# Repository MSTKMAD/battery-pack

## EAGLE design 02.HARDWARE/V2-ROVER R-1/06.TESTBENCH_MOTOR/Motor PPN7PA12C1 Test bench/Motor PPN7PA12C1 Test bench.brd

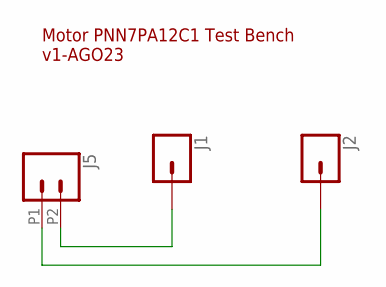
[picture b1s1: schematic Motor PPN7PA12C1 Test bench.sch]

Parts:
J1, J2: CONN_01; 1X01
J5: CONN_022.54MM_SCREWTERM; 1X02_2.54_SCREWTERM

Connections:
unnamed: J2.1, J5.P1 (1)
unnamed: J1.1, J5.P2 (2)

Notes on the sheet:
Motor PNN7PA12C1 Test Bench v1-AGO23

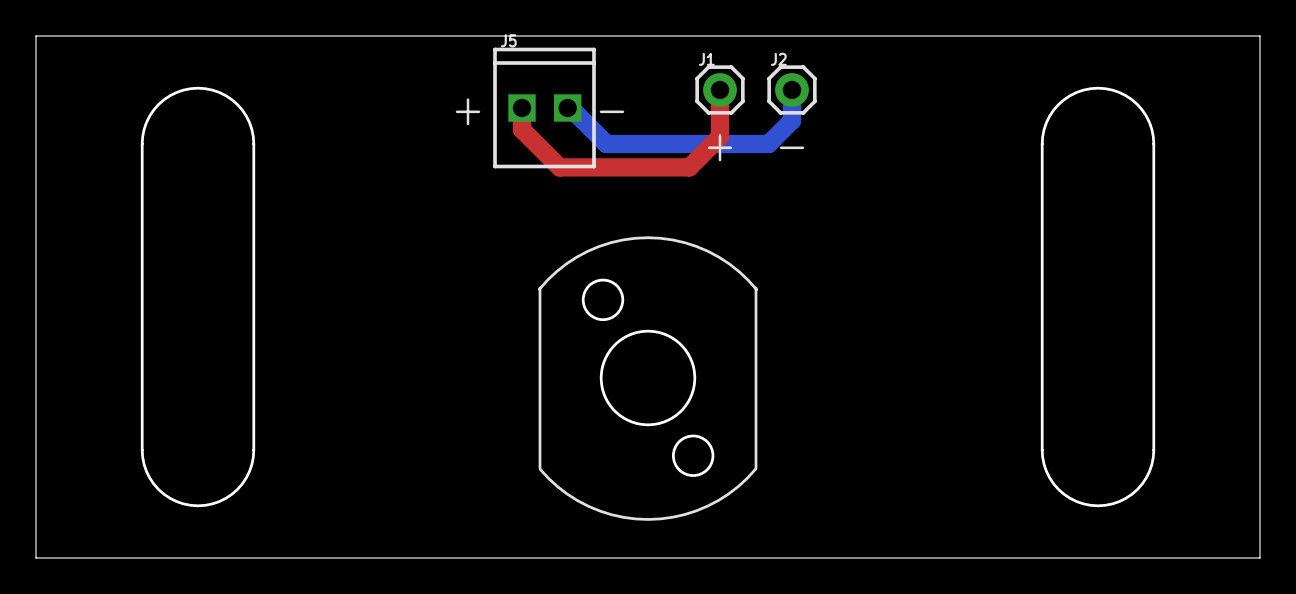
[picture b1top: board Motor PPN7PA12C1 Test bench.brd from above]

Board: 2 copper layers, 68.0 x 29.0 mm, 3 parts (0 on the bottom side), 2 nets.

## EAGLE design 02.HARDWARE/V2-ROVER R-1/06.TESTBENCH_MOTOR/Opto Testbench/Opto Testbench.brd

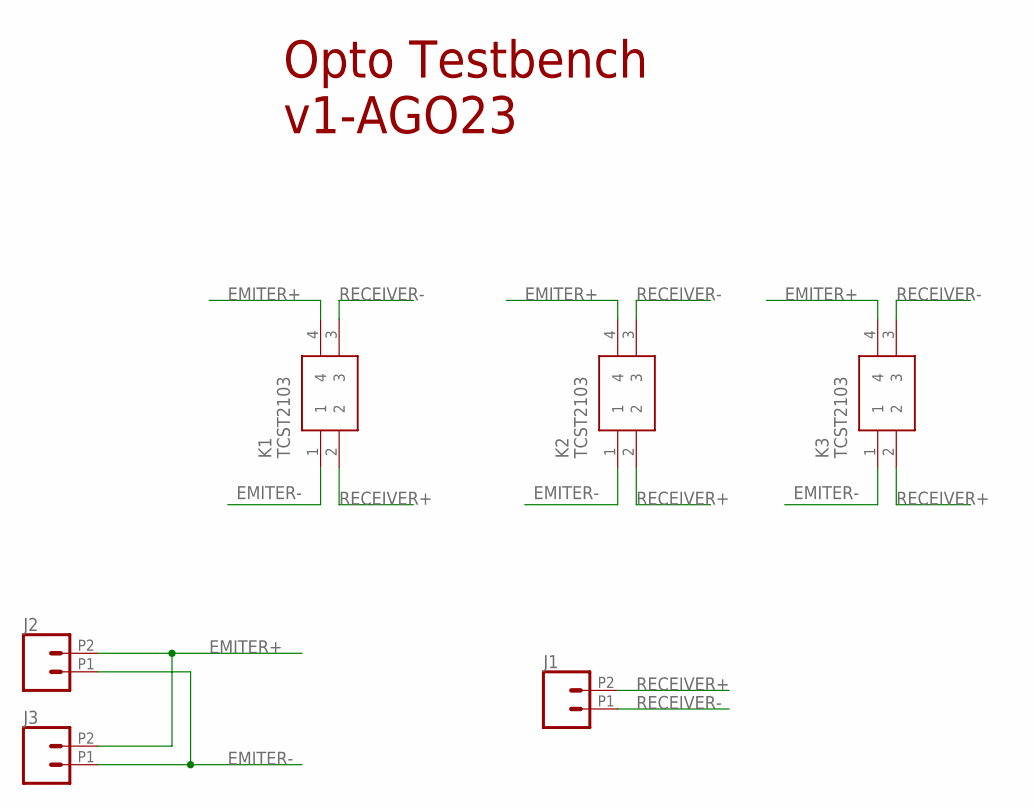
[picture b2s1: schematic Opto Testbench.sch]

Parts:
J1, J2, J3: CONN_022.54MM_SCREWTERM; 1X02_2.54_SCREWTERM
K1, K2, K3: TCST2103; DIPS254W40P760L2450H1110Q4N

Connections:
EMITER+: J2.P2 (2), J3.P2 (2), K1.4, K2.4, K3.4
EMITER-: J2.P1 (1), J3.P1 (1), K1.1, K2.1, K3.1
RECEIVER+: J1.P2 (2), K1.2, K2.2, K3.2
RECEIVER-: J1.P1 (1), K1.3, K2.3, K3.3

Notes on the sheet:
Opto Testbench v1-AGO23

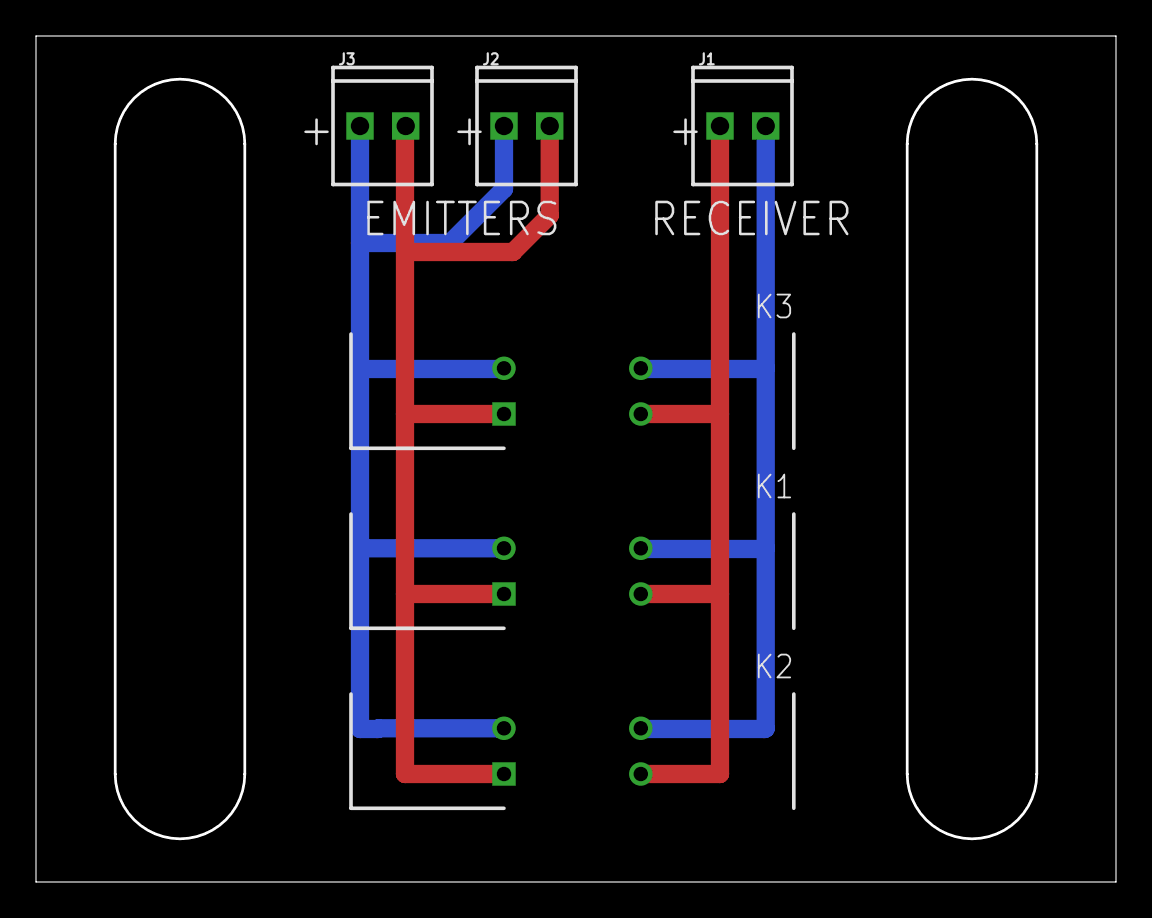
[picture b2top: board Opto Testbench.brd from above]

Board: 2 copper layers, 60.0 x 47.0 mm, 6 parts (0 on the bottom side), 4 nets.

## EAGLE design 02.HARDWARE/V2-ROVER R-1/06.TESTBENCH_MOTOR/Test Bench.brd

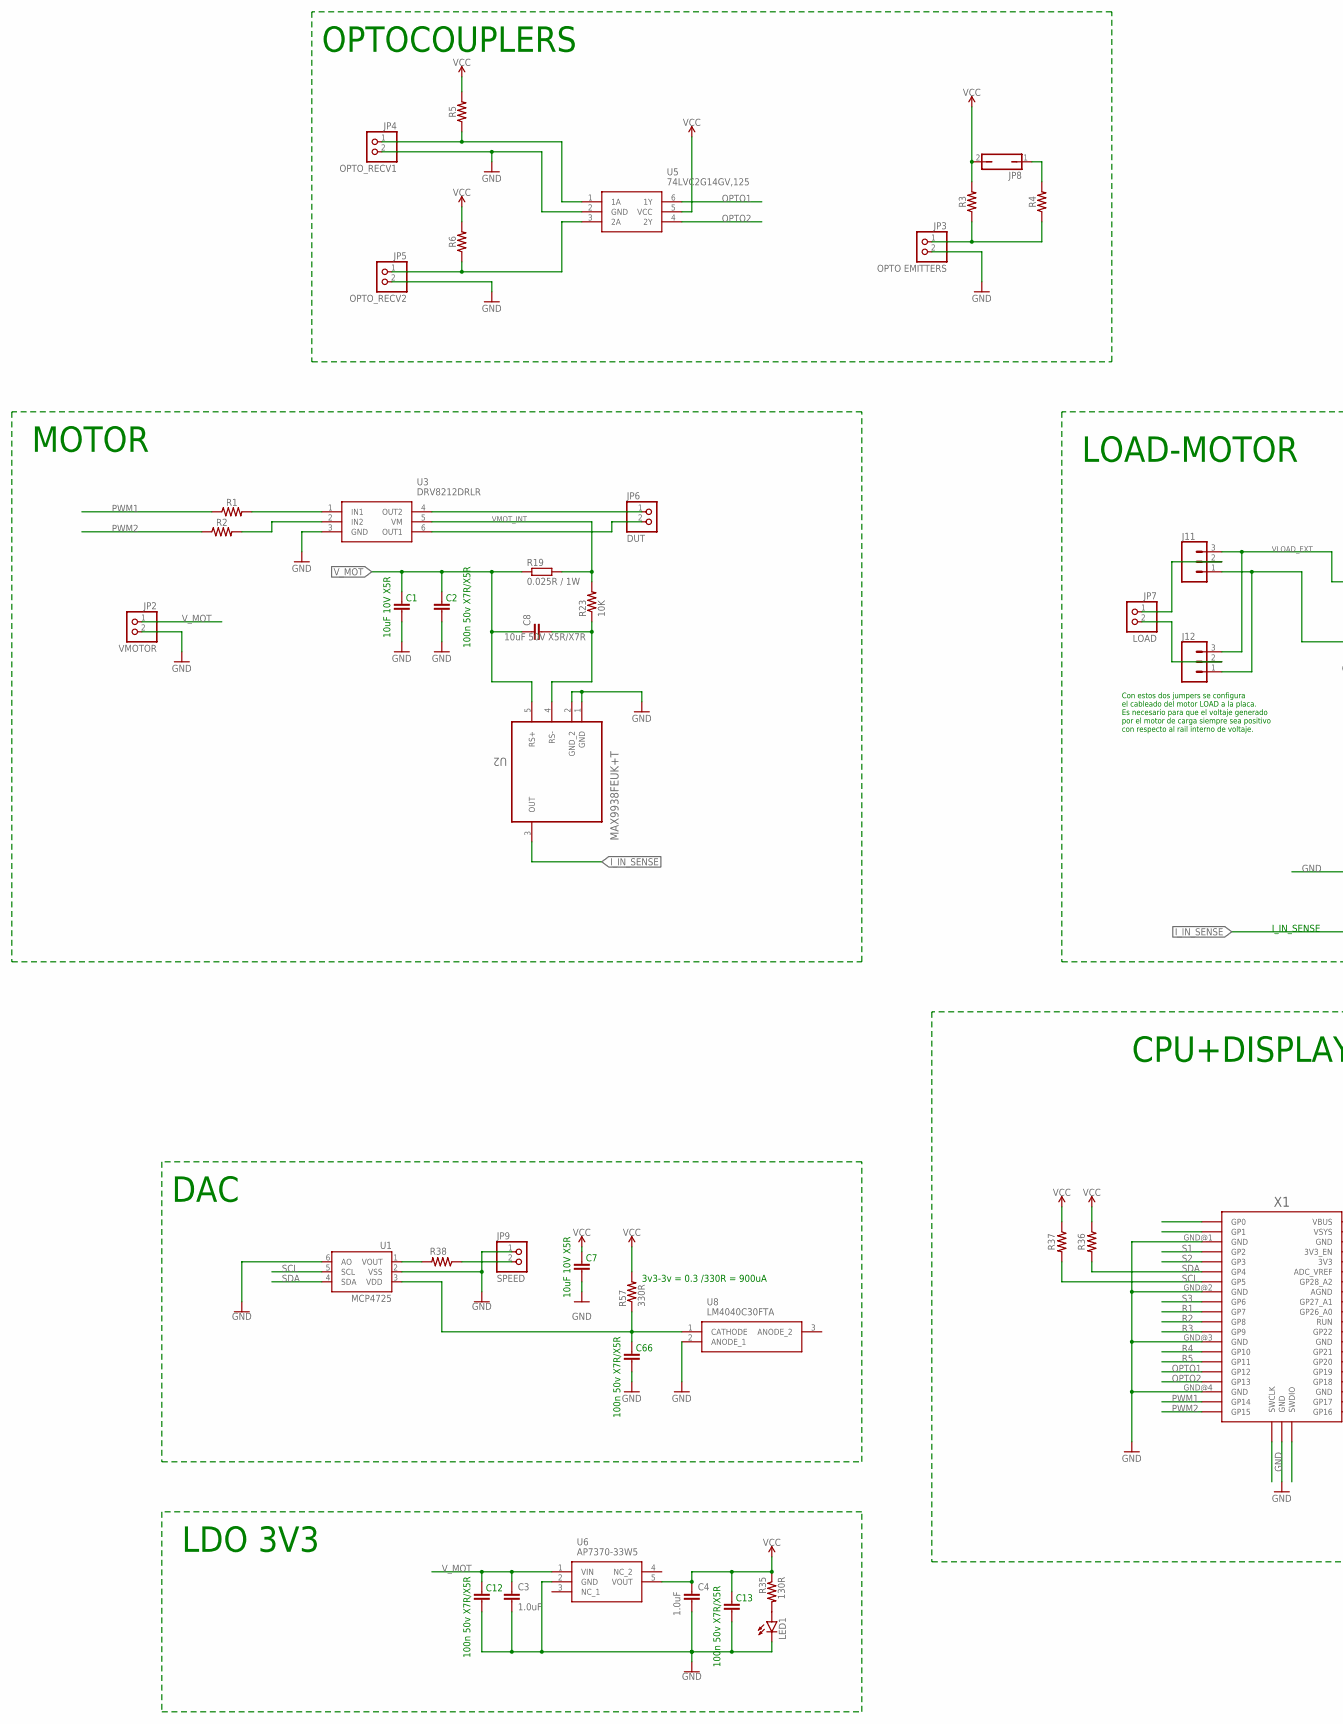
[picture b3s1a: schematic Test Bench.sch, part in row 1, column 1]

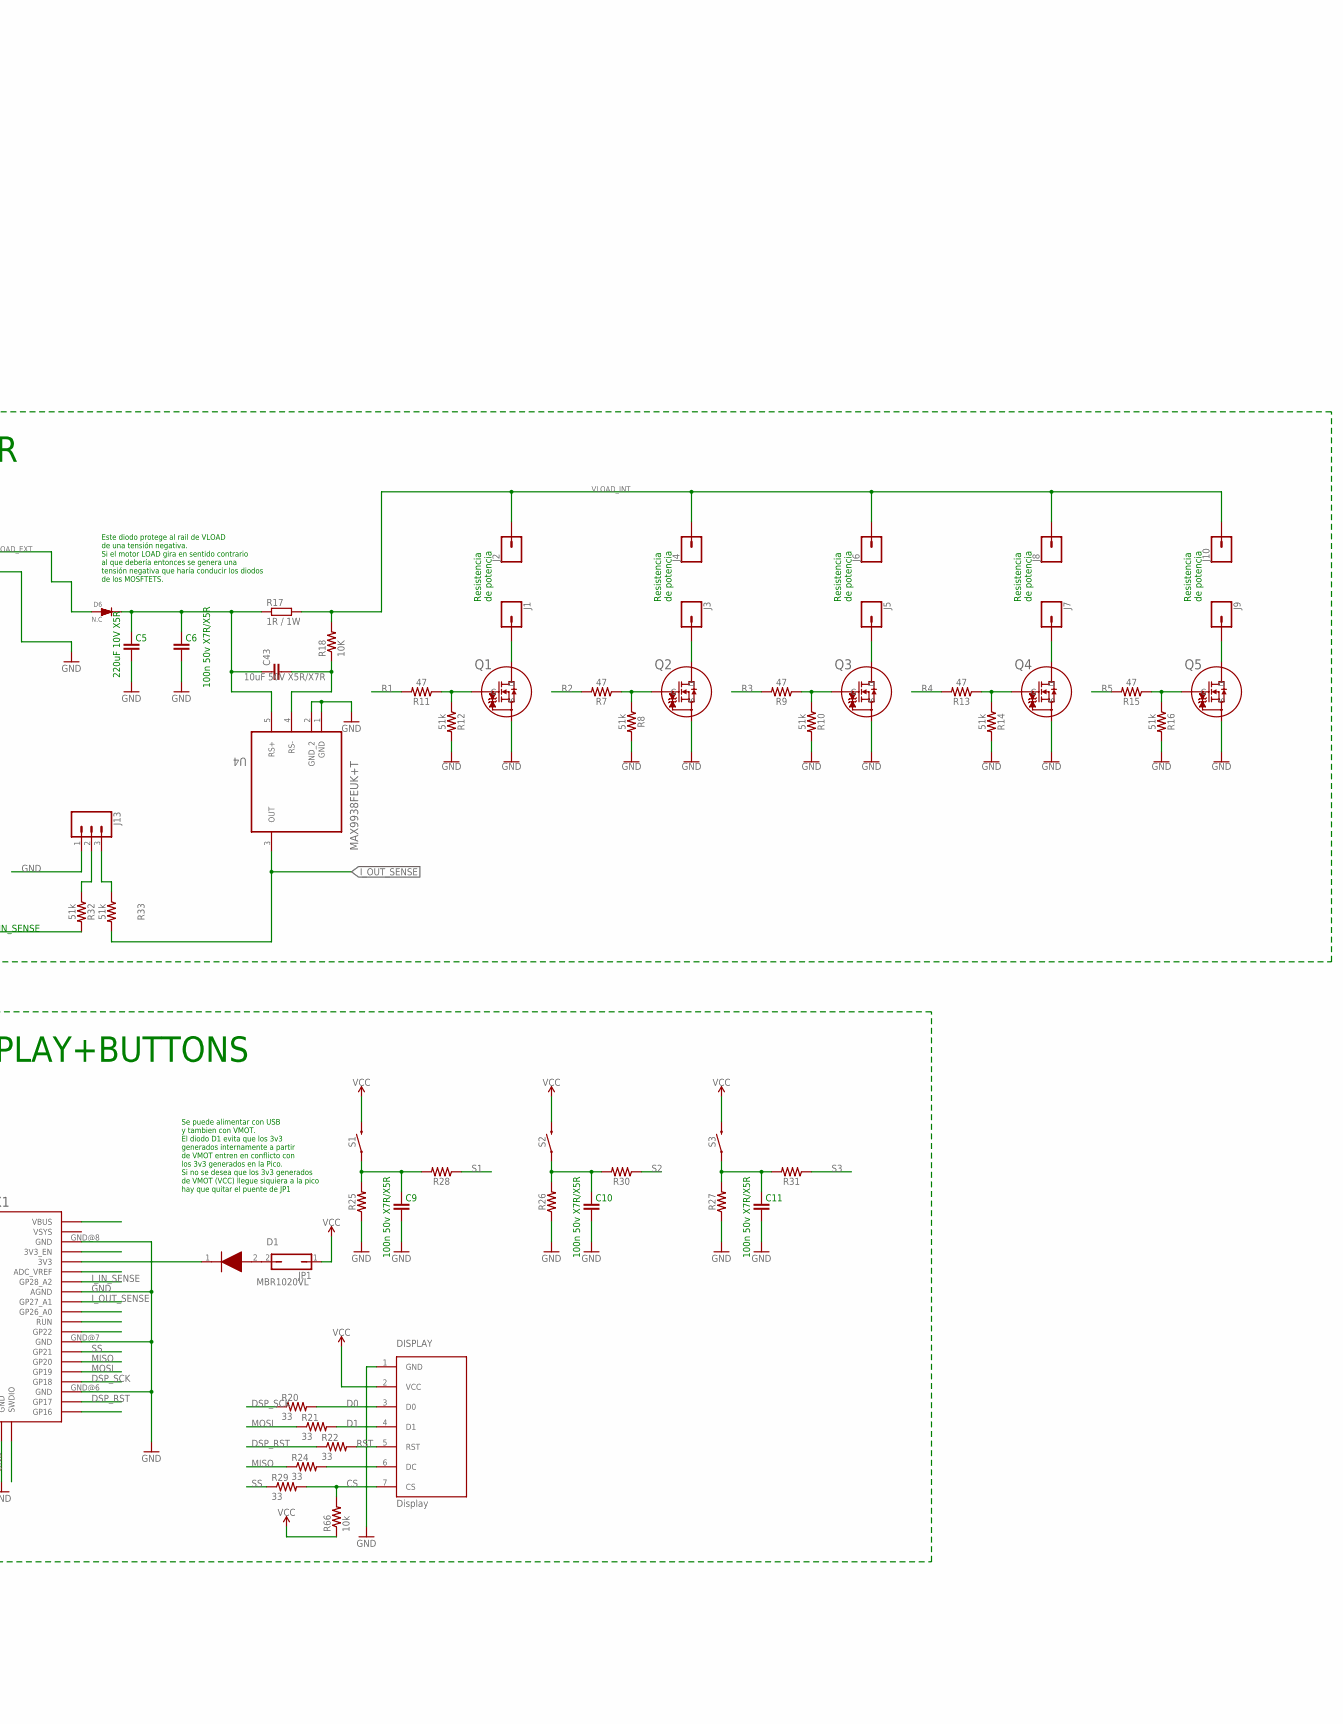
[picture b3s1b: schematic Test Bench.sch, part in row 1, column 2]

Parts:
C1, C7: 10uF 10V X5R; 0805
C2, C6, C9, C10, C11, C12, C13, C66: 100n 50v X7R/X5R; 0805
C3, C4: 1.0uF; 0805
C5: 220uF 10V X5R; 0805
C8, C43: 10uF 50V X5R/X7R; 1206
D1: MBR1020VL; SODFL3617X108N
D6: N.C; DO-214AB
DISPLAY: Display; OLED_LCD
J1, J2, J3, J4, J5, J6, J7, J8, J9, J10: CONN_01; 1X01
J11, J12, J13: CONN_03; 1X03
JP1, JP8: JP1Q; JP1
JP2: VMOTOR; 1X02
JP3: OPTO EMITTERS; 1X02
JP4: OPTO_RECV1; 1X02
JP5: OPTO_RECV2; 1X02
JP6: DUT; 1X02
JP7: LOAD; 1X02
JP9: SPEED; 1X02
LED1: LED3MM
Q1, Q2, Q3, Q4, Q5: PJA3416AE_R1_00001; SOT23_PJA3416_PNJ
R1, R2, R3, R4, R5, R6, R25, R26, R27, R28, R30, R31, R36, R37: 0805
R7, R9, R11, R13, R15: 47; 0805
R8, R10, R12, R14, R16, R32, R33: 51k; 0805
R17: 1R / 1W; R2512
R18, R23: 10K; 0805
R19: 0.025R / 1W; R2512
R20, R21, R22, R24, R29: 33; 0805
R35: 130R; 0805
R38: RESISTOR0805; 0805
R57: 330R; 0805
R66: 10k; 0805
S1, S2, S3: MOMENTARY-SWITCH-SPST-SMD-5.2MM; TACTILE_SWITCH_SMD_5.2MM
U1: MCP4725; SOT23-6
U2, U4: MAX9938FEUK+T; SOT95P280X145-5N
U3: DRV8212DRLR; SOTFL50P160X60-6N
U5: 74LVC2G14GV,125; SOT95P275X110-6N
U6: AP7370-33W5; SOT95P285X140-5N
U8: LM4040C30FTA; SOT96P240X120-3N
X1: RPI_PICO_IG-TH; RPI_PICO_TH

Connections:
3V_REF: C66.2, R57.1, U1.3 (VDD), U8.1 (CATHODE)
CS: DISPLAY.7 (CS), R29.2, R66.2
D0: DISPLAY.3 (D0), R20.2
D1: DISPLAY.4 (D1), R21.2
DSP_RST: R22.1, X1.GP17
DSP_SCK: R20.1, X1.GP18
GND: C1.1, C2.1, C3.2, C4.2, C5.1, C6.1, C7.1, C9.1, C10.1, C11.1, C12.1, C13.1, C66.1, DISPLAY.1 (GND), J11.1, J12.1, J13.1, JP2.2, JP3.2, JP4.2, JP5.2, JP9.1, LED1.K (C), Q1.2 (S), Q2.2 (S), Q3.2 (S), Q4.2 (S), Q5.2 (S), R8.2, R10.2, R12.2, R14.2, R16.2, R25.1, R26.1, R27.1, U1.2 (VSS), U1.6 (AO), U2.1 (GND), U2.2 (GND_2), U3.3 (GND), U4.1 (GND), U4.2 (GND_2), U5.2 (GND), U6.2 (GND), U8.2 (ANODE_1), X1.AGND, X1.GND@1 (GND), X1.GND@2 (GND), X1.GND@3 (GND), X1.GND@4 (GND), X1.GND@5 (GND), X1.GND@6 (GND), X1.GND@7 (GND), X1.GND@8 (GND)
I_IN_SENSE: R32.2, U2.3 (OUT), X1.GP28_A2
I_OUT_SENSE: R33.2, U4.3 (OUT), X1.GP27_A1
MISO: R24.1, X1.GP20
MOSI: R21.1, X1.GP19
unnamed: J13.2, R32.1
unnamed: JP3.1, R3.1, R4.1
unnamed: J9.1, Q5.3 (D)
unnamed: JP8.1, R4.2
unnamed: JP4.1, R5.1, U5.1 (1A)
unnamed: JP5.1, R6.1, U5.3 (2A)
unnamed: JP6.2, U3.6 (OUT1)
unnamed: R38.2, U1.1 (VOUT)
unnamed: J13.3, R33.1
unnamed: JP6.1, U3.4 (OUT2)
unnamed: R1.2, U3.1 (IN1)
unnamed: R2.2, U3.2 (IN2)
unnamed: Q2.1 (G), R7.1, R8.1
unnamed: Q3.1 (G), R9.1, R10.1
unnamed: Q4.1 (G), R13.1, R14.1
unnamed: DISPLAY.6 (DC), R24.2
unnamed: Q5.1 (G), R15.1, R16.1
unnamed: JP9.2, R38.1
unnamed: Q1.1 (G), R11.1, R12.1
unnamed: J11.2, JP7.1
unnamed: D1.2 (A), JP1.2
unnamed: J12.2, JP7.2
unnamed: J1.1, Q1.3 (D)
unnamed: J3.1, Q2.3 (D)
unnamed: J5.1, Q3.3 (D)
unnamed: J7.1, Q4.3 (D)
unnamed: C9.2, R25.2, R28.2, S1.1
unnamed: C10.2, R26.2, R30.2, S2.1
unnamed: C43.2, R18.1, U4.4 (RS-)
unnamed: D1.1 (K), X1.3V3
unnamed: C8.2, R23.1, U2.4 (RS-)
unnamed: LED1.A, R35.2
unnamed: C11.2, R27.2, R31.2, S3.1
OPTO1: U5.6 (1Y), X1.GP12
OPTO2: U5.4 (2Y), X1.GP13
PWM1: R1.1, X1.GP14
PWM2: R2.1, X1.GP15
R1: R11.2, X1.GP7
R2: R7.2, X1.GP8
R3: R9.2, X1.GP9
R4: R13.2, X1.GP10
R5: R15.2, X1.GP11
RST: DISPLAY.5 (RST), R22.2
S1: R28.1, X1.GP2
S2: R30.1, X1.GP3
S3: R31.1, X1.GP6
SCL: R37.2, U1.5 (SCL), X1.GP5
SDA: R36.2, U1.4 (SDA), X1.GP4
SS: R29.1, X1.GP21
VCC: C4.1, C7.2, C13.2, DISPLAY.2 (VCC), JP1.1, JP8.2, R3.2, R5.2, R6.2, R35.1, R36.1, R37.1, R57.2, R66.1, S1.3 (2), S2.3 (2), S3.3 (2), U5.5 (VCC), U6.5 (VOUT)
VLOAD_EXT: D6.1 (A), J11.3, J12.3
VLOAD_INT: J2.1, J4.1, J6.1, J8.1, J10.1, R17.2, R18.2
VMOT_INT: R19.2, R23.2, U3.5 (VM)
VOLAD_EXT2: C5.2, C6.2, C43.1, D6.2 (K), R17.1, U4.5 (RS+)
V_MOT: C1.2, C2.2, C3.1, C8.1, C12.2, JP2.1, R19.1, U2.5 (RS+), U6.1 (VIN)

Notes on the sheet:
Resistencia de potencia
3v3-3v = 0.3 /330R = 900uA
I_IN_SENSE
DAC
MOTOR
OPTOCOUPLERS
LOAD-MOTOR
CPU+DISPLAY+BUTTONS
LDO 3V3
Se puede alimentar con USB y tambien con VMOT. El diodo D1 evita que los 3v3 generados internamente a partir de VMOT entren en conflicto con los 3v3 generados en la Pico. Si no se desea que los 3v3 generados de VMOT (VCC) llegue siquiera a la pico hay que quitar el puente de JP1
Este diodo protege al rail de VLOAD de una tensión negativa. Si el motor LOAD gira en sentido contrario al que debería entonces se genera una tensión negativa que haría conducir los diodos de los MOSFTETS.
Con estos dos jumpers se configura el cableado del motor LOAD a la placa. Es necesario para que el voltaje generado por el motor de carga siempre sea positivo con respecto al rail interno de voltaje.

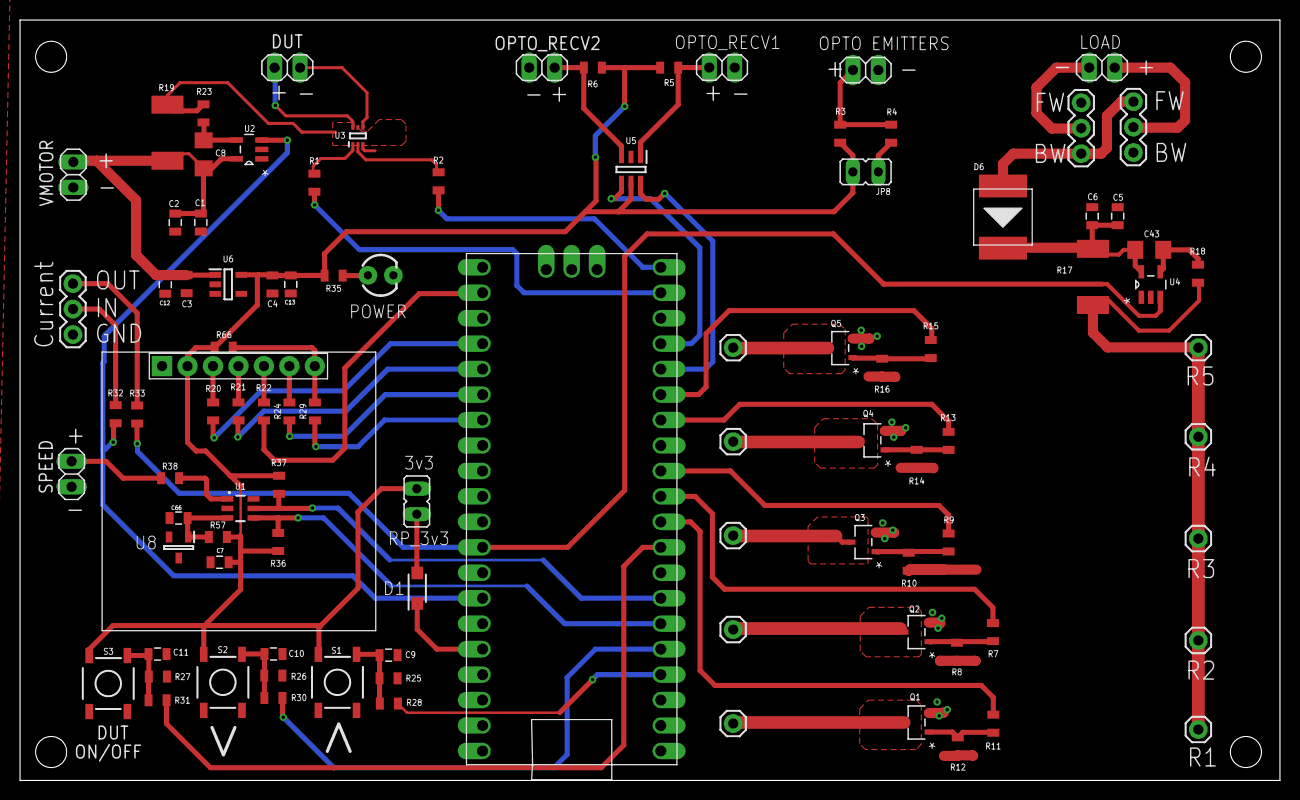
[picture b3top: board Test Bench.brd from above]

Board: 2 copper layers, 125.7 x 75.9 mm, 96 parts (0 on the bottom side), 66 nets.

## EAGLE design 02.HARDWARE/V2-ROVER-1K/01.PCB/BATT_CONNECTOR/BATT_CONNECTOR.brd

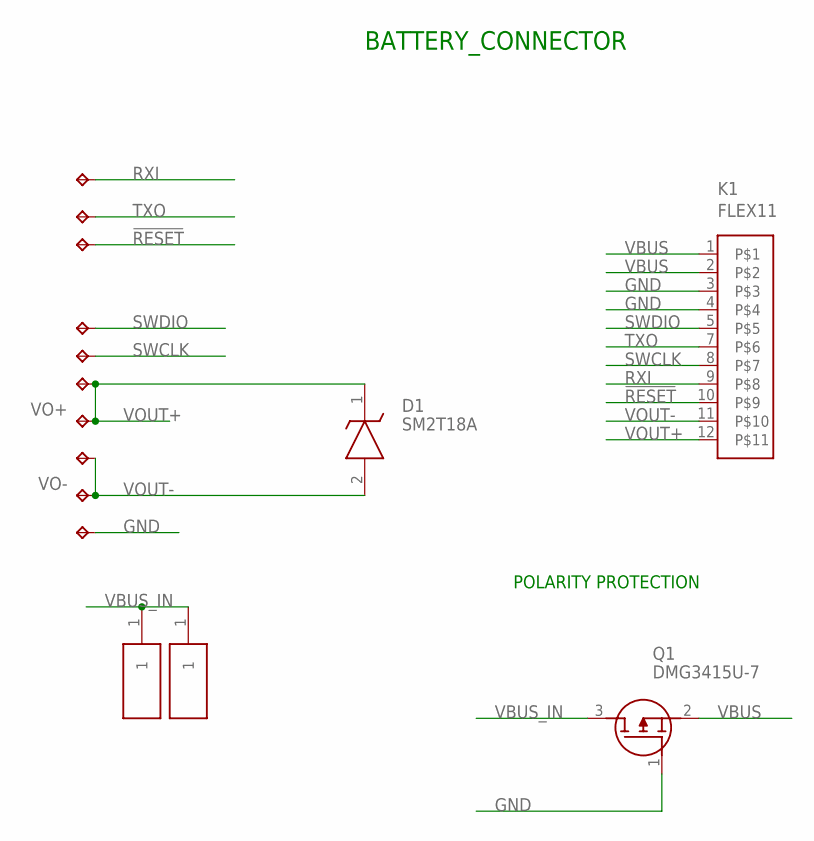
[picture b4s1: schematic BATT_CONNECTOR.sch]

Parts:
!RESET: TPB2,54; B2,54
D1: SM2T18A
GND: TPB2,54; B2,54
H1, H2: S1761-42R; S176142R
K1: FLEX11
Q1: DMG3415U-7; SSM3J332RLFT
RXI: TPB2,54; B2,54
SWCLK: TPB2,54; B2,54
SWDIO: TPB2,54; B2,54
TXO: TPB2,54; B2,54
VO+: TPB2,54; B2,54
VO-: TPB2,54; B2,54
VOUT+1: TPB2,54; B2,54
VOUT-1: TPB2,54; B2,54

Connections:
!RESET: !RESET.TP, K1.10
GND: GND.TP, K1.3, K1.4, Q1.1 (G)
RXI: K1.9, RXI.TP
SWCLK: K1.8, SWCLK.TP
SWDIO: K1.5, SWDIO.TP
TXO: K1.7, TXO.TP
VBUS: K1.1, K1.2, Q1.2 (S)
VBUS_IN: H1.1, H2.1, Q1.3 (D)
VOUT+: D1.1 (K), K1.12, VO+.TP, VOUT+1.TP
VOUT-: D1.2 (A), K1.11, VO-.TP, VOUT-1.TP

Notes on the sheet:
POLARITY PROTECTION
BATTERY_CONNECTOR

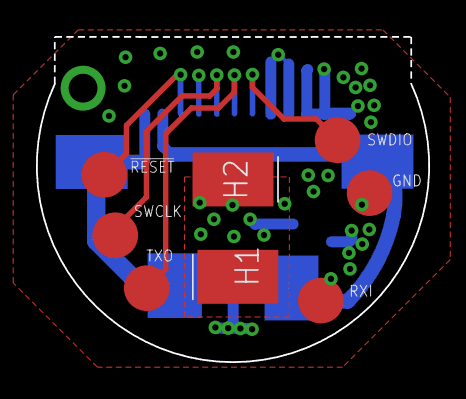
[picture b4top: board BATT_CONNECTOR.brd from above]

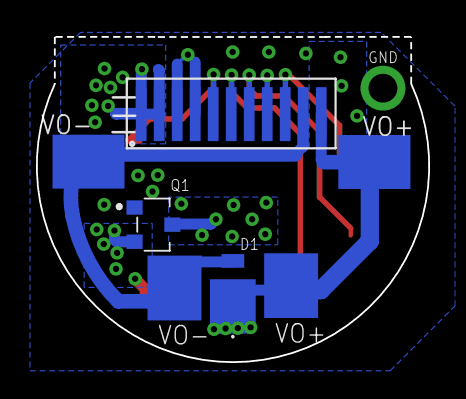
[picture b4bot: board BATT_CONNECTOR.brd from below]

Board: 4 copper layers, 21.8 x 18.1 mm, 15 parts (7 on the bottom side), 10 nets.

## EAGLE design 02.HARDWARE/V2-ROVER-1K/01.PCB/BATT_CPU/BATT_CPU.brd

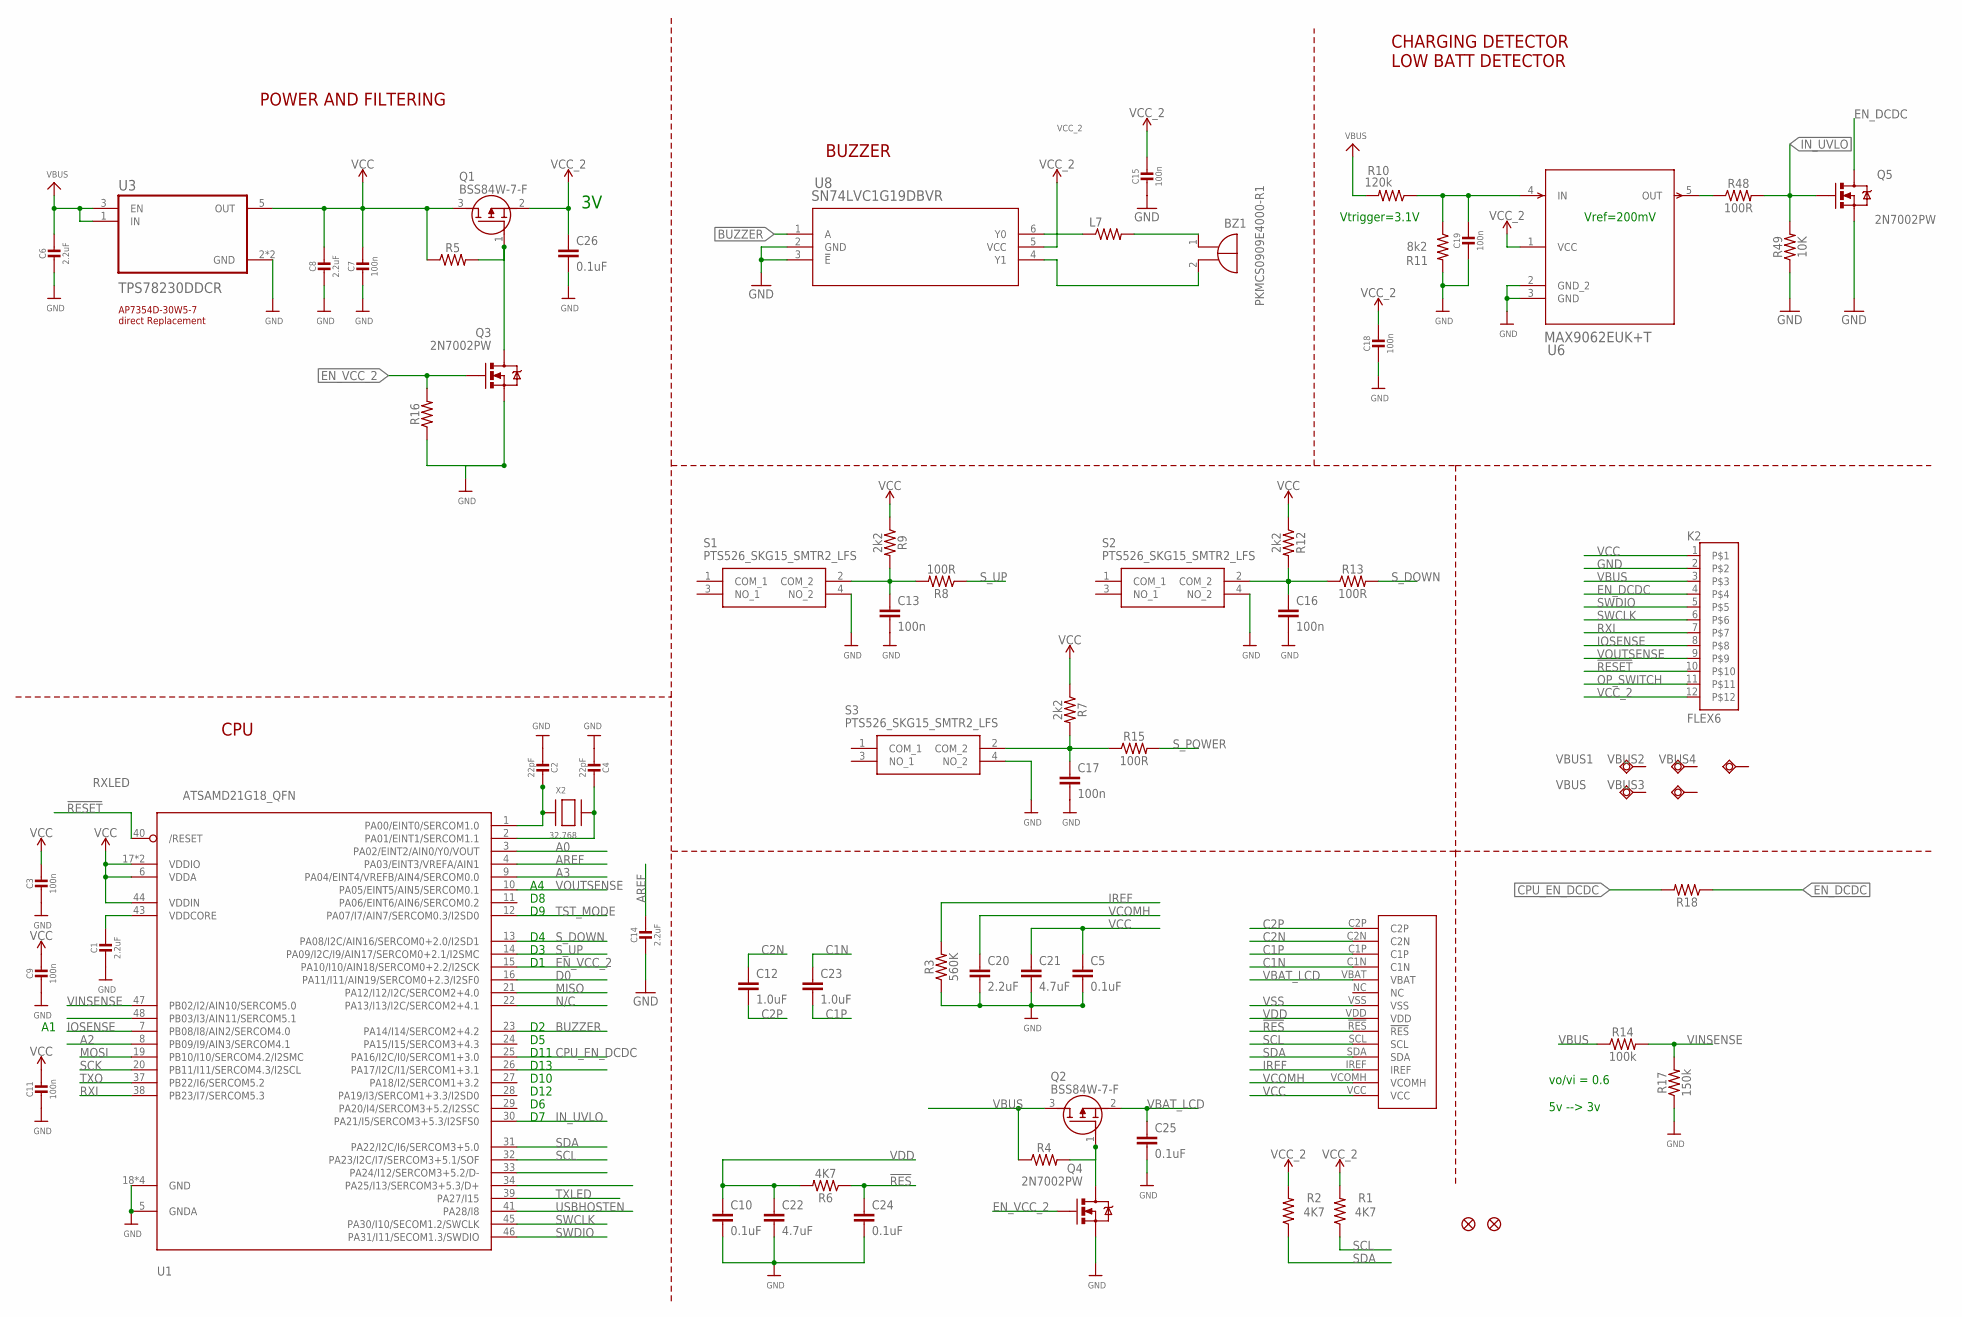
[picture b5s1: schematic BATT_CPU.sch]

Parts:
BZ1: PKMCS0909E4000-R1; PKMCS0909
C1, C14: 2.2uF; 0603-NO
C2, C4: 22pF; 0603-NO
C3, C7, C9, C11, C15, C18, C19: 100n; 0603-NO
C5, C10, C24, C25, C26: 0.1uF; 0402
C6, C8: 2.2uF; 0805-NO
C12, C23: 1.0uF; 0402
C13, C16, C17: 100n; C0805
C20: 2.2uF; 0603
C21, C22: 4.7uF; 0603
K2: FLEX6
L7: MMZ2012Y202BT000; 0805
Q1, Q2: BSS84W-7-F; SOT65P222X110-3N
Q3, Q4, Q5: 2N7002PW; SOT323
R1, R2, R6: 4K7; 0402
R3: 560K; 0402
R4, R5, R16, R18: 0402
R7, R9, R12: 2k2; 0402
R8, R13, R15, R48: 100R; 0402
R10: 120k; 0402
R11: 8k2; 0402
R14: 100k; 0402
R17: 150k; 0402
R49: 10K; 0402
S1, S2, S3: PTS526_SKG15_SMTR2_LFS; PTS526SKG15SMTR2LFS
U1: ATSAMD21G18_QFN; TQFN48_7MM
U3: TPS78230DDCR; SOT95P280X110-5N
U6: MAX9062EUK+T; 21-0057F_MXM
U8: SN74LVC1G19DBVR; DBV6
U$30: 64X32_OLED_049; LCD_14_PINS
U$34, U$35: FIDUCIAL""; FIDUCIAL_1MM
VBUS, VBUS1, VBUS2, VBUS3, VBUS4: TESTPAD_TPSQB1,27; TESTPAD_B1,27
X2: 32.768; XTAL3215

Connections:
!RES: C24.1, R6.1, U$30.!RES
!RESET: K2.10, U1.40 (/RESET)
A0: U1.3 (PA02/EINT2/AIN0/Y0/VOUT)
A2: U1.8 (PB09/I9/AIN3/SERCOM4.1)
A3: U1.9 (PA04/EINT4/VREFB/AIN4/SERCOM0.0)
AREF: C14.1, U1.4 (PA03/EINT3/VREFA/AIN1)
BUZZER: U1.23 (PA14/I14/SERCOM2+4.2), U8.1 (A)
C1N: C23.1, U$30.C1N
C1P: C23.2, U$30.C1P
C2N: C12.1, U$30.C2N
C2P: C12.2, U$30.C2P
CPU_EN_DCDC: R18.2, U1.25 (PA16/I2C/I0/SERCOM1+3.0)
D0: U1.16 (PA11/I11/AIN19/SERCOM0+2.3/I2SF0)
EN_DCDC: K2.4, Q5.3 (D), R18.1
EN_VCC_2: Q3.1 (G), Q4.1 (G), R16.2, U1.15 (PA10/I10/AIN18/SERCOM0+2.2/I2SCK)
GND: C1.2, C2.2, C3.2, C4.2, C5.2, C6.2, C7.2, C8.2, C9.2, C10.2, C11.2, C13.2, C14.2, C15.2, C16.2, C17.2, C18.2, C19.2, C20.2, C21.2, C22.2, C24.2, C25.2, C26.2, K2.2, Q3.2 (S), Q4.2 (S), Q5.2 (S), R3.1, R11.2, R16.1, R17.1, R49.1, S1.4 (NO_2), S2.4 (NO_2), S3.4 (NO_2), U1.5 (GNDA), U1.18 (GND), U1.35 (GND), U1.42 (GND), U1.THERMAL (GND), U3.2 (GND), U3.4 (GND), U6.2 (GND_2), U6.3 (GND), U8.2 (GND), U8.3 (!E)
IN_UVLO: Q5.1 (G), R48.2, R49.2, U1.30 (PA21/I5/SERCOM3+5.3/I2SFS0)
IOSENSE: K2.8, U1.7 (PB08/I8/AIN2/SERCOM4.0)
IREF: R3.2, U$30.IREF
MISO: U1.21 (PA12/I12/I2C/SERCOM2+4.0)
MOSI: U1.19 (PB10/I10/SERCOM4.2/I2SMC)
unnamed: C17.1, R7.2, R15.1, S3.2 (COM_2)
unnamed: C13.1, R8.2, R9.2, S1.2 (COM_2)
unnamed: C16.1, R12.2, R13.1, S2.2 (COM_2)
unnamed: Q2.1 (G), Q4.3 (D), R4.2
unnamed: C2.1, U1.1 (PA00/EINT0/SERCOM1.0), X2.P$1
unnamed: Q1.1 (G), Q3.3 (D), R5.2
unnamed: C4.1, U1.2 (PA01/EINT1/SERCOM1.1), X2.P$2
unnamed: C19.1, R10.1, R11.1, U6.4 (IN)
unnamed: L7.1, U8.6 (Y0)
unnamed: BZ1.1 (+), L7.2
unnamed: BZ1.2 (-), U8.4 (Y1)
unnamed: R48.1, U6.5 (OUT)
OP_SWITCH: K2.11, U1.26 (PA17/I2C/I1/SERCOM1+3.1)
RXI: K2.7, U1.38 (PB23/I7/SERCOM5.3)
SCK: U1.20 (PB11/I11/SERCOM4.3/I2SCL)
SCL: R1.1, U1.32 (PA23/I2C/I7/SERCOM3+5.1/SOF), U$30.SCL
SDA: R2.1, U1.31 (PA22/I2C/I6/SERCOM3+5.0), U$30.SDA
SWCLK: K2.6, U1.45 (PA30/I10/SECOM1.2/SWCLK)
SWDIO: K2.5, U1.46 (PA31/I11/SECOM1.3/SWDIO)
S_DOWN: R13.2, U1.13 (PA08/I2C/AIN16/SERCOM0+2.0/I2SD1)
S_POWER: R15.2
S_UP: R8.1, U1.14 (PA09/I2C/I9/AIN17/SERCOM0+2.1/I2SMC)
TST_MODE: U1.12 (PA07/I7/AIN7/SERCOM0.3/I2SD0)
TXO: U1.37 (PB22/I6/SERCOM5.2)
VBAT_LCD: C25.1, Q2.2 (S), U$30.VBAT
VBUS: C6.1, K2.3, Q2.3 (D), R4.1, R10.2, R14.1, U3.1 (IN), U3.3 (EN)
VCC: C3.1, C5.1, C7.1, C8.1, C9.1, C11.1, C21.1, K2.1, Q1.3 (D), R5.1, R7.1, R9.1, R12.1, U1.6 (VDDA), U1.17 (VDDIO), U1.36 (VDDIO), U1.44 (VDDIN), U3.5 (OUT), U$30.VCC
VCC_2: C15.1, C18.1, C26.1, K2.12, Q1.2 (S), R1.2, R2.2, U6.1 (VCC), U8.5 (VCC)
VCOMH: C20.1, U$30.VCOMH
VDD: C10.1, C22.1, R6.2, U$30.VDD
VDDCORE: C1.1, U1.43 (VDDCORE)
VINSENSE: R14.2, R17.2, U1.47 (PB02/I2/AIN10/SERCOM5.0)
VOUTSENSE: K2.9, U1.10 (PA05/EINT5/AIN5/SERCOM0.1)
VSS: U$30.VSS

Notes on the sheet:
POWER AND FILTERING
N/C
TXLED
USBHOSTEN
RXLED
BUZZER
AP7354D-30W5-7 direct Replacement
D10
CHARGING DETECTOR LOW BATT DETECTOR
CPU
Vref=200mV
Vtrigger=3.1V
D13
D11
D12
vo/vi = 0.6 5v --> 3v

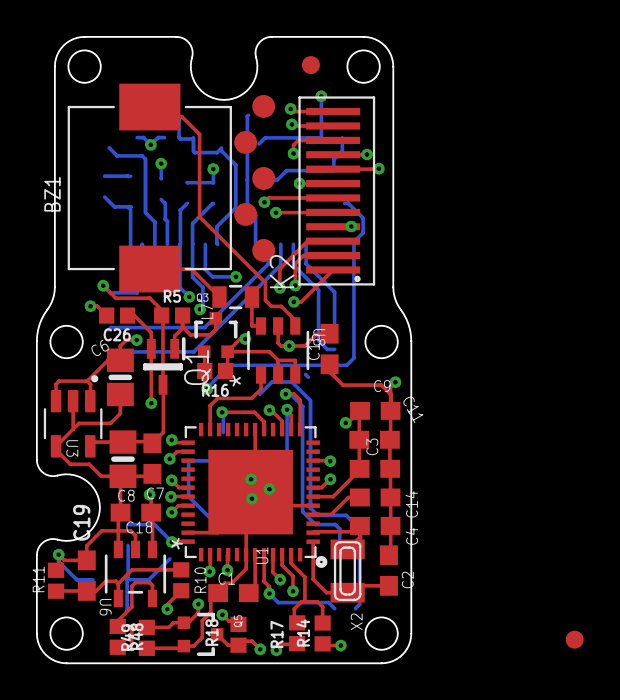
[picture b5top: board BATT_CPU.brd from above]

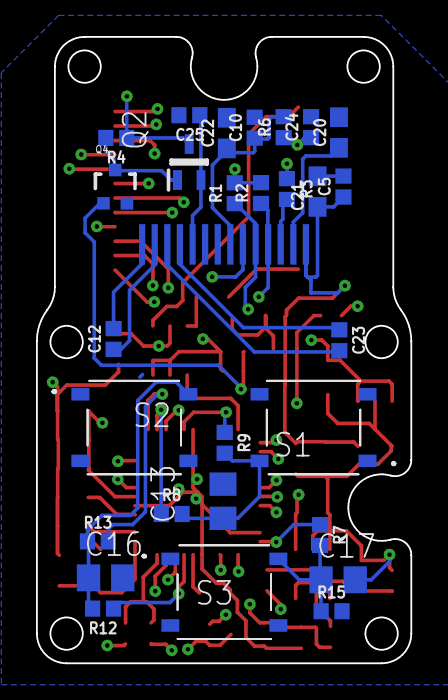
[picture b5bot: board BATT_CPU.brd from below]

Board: 4 copper layers, 20.8 x 34.8 mm, 70 parts (29 on the bottom side), 44 nets.

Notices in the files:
parts and their libraries:
SparkFun-Connectors: Licensing: Creative Commons ShareAlike 4.0 International - https://creativecommons.org/licenses/by-sa/4.0
COPYRIGHT: Copyright (C) 2022 Ultra Librarian. All rights reserved.
